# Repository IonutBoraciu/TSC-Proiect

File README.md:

# OpenBook, Boraciu Ionut-Sorin 335CA

# Description 

 OpenBook is an open-source, affordable e-book reader designed for mass production. The project focuses on accessibility, cost efficiency, and user control, providing a customizable reading experience with open hardware and software.

# Table of contents
1. [Description](#description)
2. [E-Book Reader Diagram](#e-book-reader-diagram)
3. [Bill of materials (BOM)](#bill-of-materials-bom)
4. [Hardware Functionality Description](#hardware-functionality-description)
5. [Estimated Power Consumption 🔋](#estimated-power-consumption-)
6. [Total estimated power consumtion ( assuming wifi active) 🔋](#total-estimated-power-consumtion--assuming-wifi-active-)
7. [Estimated battery life](#estimated-battery-life)
8. [ESP32-C6 Pin Usage](#esp32-c6-pin-usage)
9. [Pins explanation](#pins-explanation)
10. [Final Product](#final-product)

 # E-Book Reader Diagram

 # Bill of materials (BOM)
 | 🛠 Component | 🔗 Link | 📄 Datasheet |
 |-------------|--------|------------|
 | 112A-TAAR-R03_ATTEND |[Comet](https://store.comet.srl.ro/Catalogue/Product/43497/) | [Datasheet](https://store.comet.bg/download-file.php?id=27596) |
 | 744043680IND | [Mouser](https://eu.mouser.com/ProductDetail/Wurth-Elektronik/744043680?qs=PGXP4M47uW6VkZq%252BkzjrHA%3D%3D) | [Datasheet](https://www.we-online.com/components/products/datasheet/744043680.pdf) |
 | ADAFRUIT_LEDCHIP | [SnapMagic](https://www.snapeda.com/parts/KP-1608SURCK/Kingbright/view-part/?ref=search&t=LED%200603) | [Datasheet](https://www.snapeda.com/parts/KP-1608SURCK/Kingbright/datasheet/) |
 | BD5229G-TR | [Component Search Engine](https://componentsearchengine.com/part-view/BD5229G-TR/ROHM%20Semiconductor) | [Datasheet](https://datasheet.datasheetarchive.com/originals/distributors/Datasheets_SAMA/f2b9741ef86007909f138d561a359946.pdf) |
 | BUTTON_CUSYOMV1 | [Panasonic](https://industry.panasonic.com/global/en/products/control/switch/light-touch/number/evqpuj02k) | [Datasheet](https://industry.panasonic.com/global/en/downloads?tab=catalog&small_g_cd=203&part_no=EVQPUJ02K&q=RVZRUFVKMDJLJTdDMTMlN0MyMDMlN0MzNDU5JTdDMSU3QyU3QzIlN0NmYWxzZQ%3D%3D) |
 | CPH3225A | [SnapMagic](https://www.snapeda.com/parts/CPH3225A/Seiko+Instruments/view-part/?ref=eda) | [Datasheet](https://www.snapeda.com/parts/CPH3225A/Seiko%20Instruments/datasheet/) |
 | DS3231SN | [SnapMagic](https://www.snapeda.com/parts/DS3231SN%23/Analog+Devices/view-part/?ref=eda) | [Datasheet](https://www.snapeda.com/parts/DS3231SN%23/Analog%20Devices/datasheet/) |
 | EAGLE-LTSPICE_CC0402 | [Component Search Engine](https://componentsearchengine.com/part-view/CC0402MRX5R5BB106/YAGEO) | [Datasheet](https://componentsearchengine.com/Datasheets/2/CC0402MRX5R5BB106.pdf) |
 | ESP32-C6-WROOM-1-N8 | [SnapMagic](https://www.snapeda.com/parts/ESP32-C6-WROOM-1-N8/Espressif+Systems/view-part/?ref=eda) | [Datasheet](https://www.snapeda.com/parts/ESP32-C6-WROOM-1-N8/Espressif%20Systems/datasheet/) |
 | ESP32_WROVER_AVX | [Mouser](https://eu.mouser.com/ProductDetail/KYOCERA-AVX/SD0805S020S1R0?qs=jCA%252BPfw4LHbpkAoSnwrdjw%3D%3D) | [Datasheet](https://eu.mouser.com/datasheet/2/40/schottky-3165252.pdf) |
 | ESP32_WROVER_BME680_BME680 | [SnapMagic](https://www.snapeda.com/parts/BME680/Bosch/view-part/?welcome=home) | [Datasheet](https://www.snapeda.com/parts/BME680/Bosch%20Sensortec/datasheet/) |
 | ESP32_WROVER_EAGLE-LTSPICE_C | [Component Search Engine](https://componentsearchengine.com/part-view/CC0402MRX5R5BB106/YAGEO) | [Datasheet](https://componentsearchengine.com/Datasheets/2/CC0402MRX5R5BB106.pdf) |
 | ESP32_WROVER_EAGLE-LTSPICE_R | [Component Search Engine](https://componentsearchengine.com/part-view/R0402%201%25%20100%20K%20(RC0402FR-07100KL)/YAGEO) | [Datasheet](https://www.yageo.com/upload/media/product/products/datasheet/rchip/PYu-RC_Group_51_RoHS_L_12.pdf) |
 | ESP32_WROVER_SPARKFUN-DISCRETESEMI | [Component Search Engine](https://componentsearchengine.com/part-view/DMG2305UX-7/Diodes%20Incorporated) | [Datasheet](https://www.diodes.com//assets/Datasheets/DMG2305UX.pdf) |
 | ESP32_WROVER_SPARKFUN-IC-POWER_SOT23-5 | [Mouser](https://eu.mouser.com/ProductDetail/Microchip-Technology/MCP73831T-2ACI-OT?qs=yUQqVecv4qvbBQBGbHx0Mw%3D%3D) | [Datasheet](https://eu.mouser.com/datasheet/2/268/MCP73831_Family_Data_Sheet_DS20001984H-3441711.pdf) |
 | ESP32C6_VARISTORCN1812 | [Mouser](https://ro.mouser.com/ProductDetail/EPCOS-TDK/B72520T0350K062?qs=dEfas%2FXlABIszF52uu7vrg%3D%3D) | [Datasheet](https://www.tdk-electronics.tdk.com/inf/75/db/CTVS_14/Surge_protection_series.pdf) |
 | FH34SRJ24S05SH99 | [Component Search Engine](https://componentsearchengine.com/part-view/FH34SRJ-24S-0.5SH(99)/Hirose) | [Datasheet](https://www.hirose.com/en/product/document?clcode=CL0580-1255-6-99&productname=FH34SRJ-24S-0.5SH(99)&series=FH34SRJ&documenttype=2DDrawing&lang=en&documentid=0000990903) |
 | MAX17048G+T10 | [SnapMagic](https://www.snapeda.com/parts/MAX17048G+T10/Analog+Devices/view-part/?ref=eda) | [Datasheet](https://www.snapeda.com/parts/MAX17048G+T10/Analog%20Devices/datasheet/) |
 | MBR0530 | [Mouser](https://ro.mouser.com/ProductDetail/KYOCERA-AVX/SD0805S020S1R0?qs=jCA%252BPfw4LHbpkAoSnwrdjw%3D%3D) | [Datasheet](https://ro.mouser.com/datasheet/2/40/schottky-3165252.pdf) |
 | PGB1010603MR | [SnapMagic](https://www.snapeda.com/parts/PGB1010603MR/Littelfuse/view-part/?ref=eda) | [Datasheet](https://www.snapeda.com/parts/PGB1010603MR/Littelfuse%20Inc./datasheet/) |
 | QWIIC_CONNECTORJS | [Mouse](https://eu.mouser.com/ProductDetail/Adafruit/4208?qs=PzGy0jfpSMtbScLbr0L5dw%3D%3D) | [Datasheet](https://www.youtube.com/watch?v=Z6ACqvqwDWE) |
 | SAMACSYS_PARTS_USB4110-GF-A | [Component Search Engine](https://componentsearchengine.com/part-view/USB4110-GF-A/GCT%20(GLOBAL%20CONNECTOR%20TECHNOLOGY)) | [Datasheet](https://gct.co/files/drawings/usb4110.pdf) |
 | SI1308EDL-T1-GE3 | [Component Search Engine](https://componentsearchengine.com/part-view/SI1308EDL-T1-GE3/Vishay) | [Datasheet](https://componentsearchengine.com/Datasheets/1/SI1308EDL-T1-GE3.pdf) |
 | SJ | [GrabCAD](https://grabcad.com/library/solder-jumpers-1) | [Datasheet](https://www.youtube.com/watch?v=Z6ACqvqwDWE) |
 | USBLC6-2SC6Y | [SnapMagic](https://www.snapeda.com/parts/USBLC6-2SC6Y/STMicroelectronics/view-part/?ref=eda) | [Datasheet](https://www.snapeda.com/parts/USBLC6-2SC6Y/STMicroelectronics/datasheet/) |
 | W25Q512JVEIQ | [SnapMagic](https://www.snapeda.com/parts/W25Q512JVEIQ/Winbond+Electronics/view-part/?ref=eda) | [Datasheet](https://www.snapeda.com/parts/W25Q512JVEIQ/Winbond%20Electronics/datasheet/) |
 | XC6220A331MR-G | [Component Search Engine](https://componentsearchengine.com/part-view/XC6220A331MR-G/Torex) | [Datasheet](https://product.torexsemi.com/system/files/series/xc6220.pdf) |

# Hardware Functionality Description

### 1. Battery 🔋
 Model: CELLEVIA BATTERIES LP584174 <br>
 Specifications: 3.7V, 1800mAh  <br>
 Functionality: It is rechargeable battery, designed for portable electronic devices. It provides a stable power supply, high energy density, and a lightweight form factor. Ideal for IoT devices, wearables, embedded systems, and battery powered applications, it ensures reliable performance with a long cycle life.

 ### 2. ESP32-C6 📡
 Model: ESP32-C6-WROOM-1 <br>
 Specifications:
  * 2.4 GHz Wi-Fi 6 (802.11 ax)
  *  Bluetooth® 5 (LE) with Long Range support
  *  Zigbee and Thread(802.15.4) for low-power mesh networking  <br>
  
  Functionality: The ESP32-C6-WROOM-1 is the central controller of the project, handling all communication, control, and processing

  ### 3. E-Paper Display 📺
  Model: 7.5inch e-Paper V2 <br>
  Specifications: resolution : 800 x 480, weight ~ 44 g <br>
  Functionality: The 7.5-inch e-Paper V2 display provides a high contrast, low power visual output suitable for battery-powered applications. Unlike traditional displays, it retains content without power, making it ideal for low energy and always on applications.

 ### 4. BME688 🌡️
 Interface: I2C <br>
 Specifications:
  * Gas Sensor: Detects volatile organic compounds, carbon monoxide, hydrogen, and other gases
  * Humidity Sensor: 0–100% RH, accuracy ±3%
  * Temperature Sensor: -40°C to 85°C, accuracy ±0.5°C
  * Pressure Sensor: 300–1100 hPa, accuracy ±0.6 hPa <br>
  
 Functionality: The BME688 is an advanced environmental sensing module, providing real-time monitoring of air quality, humidity, temperature, and pressure.

 ### 5. SD Card 💾
 Interface: SPI <br>
 Functionality: it serves as expandable storage, allowing users to store a large collection of e-books, documents, and other files beyond the device's internal memory

 ### 6. RTC ⏰
 Interface: I2C <br>
 Functionality: A real-time clock (RTC) keeps track of the correct time and date, even when the device is off. It helps manage power saving features, timestamps activities like reading progress, supports reminder functions, updates time-sensitive content, and ensures proper synchronization with other devices or platforms.

 ### 7. MCP73831T ♻️🔋
 Interface: USB-C <br>
 Functionality: The MCP73831T is a compact lithium-ion and lithium-polymer battery charger IC. It features low power consumption, precharge and fast charge modes, thermal regulation, and overvoltage protection, making it ideal for portable devices.

 ### 8. External NOR Flash 64MB 🎞️
 Interface: SPI <br>
 Functionality:  non-volatile memory storage that provides 64MB of data storage. It's commonly used in embedded systems and devices for storing firmware, code, or other critical data, offering fast read speeds and reliable data retention even without power.

 ### 9. LDO Voltage Regulator ⚡
 Functionality: voltage regulator that provides a stable output voltage with minimal difference between the input and output voltages.

 ### 10. Test Pads 📝
 Functionality: deubbing and testing outputs from certain components.

 ### 11. Qwiic ✅
 Functionality: easy addition of modules through I2C and SPI.

 # Estimated Power Consumption 🔋

 ### 1. Battery (CELLEVIA BATTERIES LP584174) 🔋
  * Its power consumption depends on the load it is powering. The maximum discharge current would be around 1.8A (1800mAh)
### 2. ESP32-C6 📡
  * Wi-Fi transmission: ~200mA
  * Idle mode: ~50mA
  * Deep sleep: ~10mA
### 3. E-Paper Display 📺
  * During content update: ~30-50mA
  * Idle (static content): ~0mA (only power used for maintaining the display)
### 4. BME688 🌡️
 * Active sensing: ~2.7mA
 * Idle mode: ~0.5mA (depends on the sleep settings)
### 5. SD Card 💾
 * Typical: ~10-15 mA
### 6. RTC ⏰
* Active mode: 1- 2 mA
### 7. MCP73831T ♻️🔋
*  Minimal power consumption
### 8. External NOR Flash 64MB 🎞️
* Active read/write: ~10-20mA
* Idle: <1mA
### 9. LDO Voltage Regulator ⚡
 * Idle mode: ~1-10mA (depends on the output load)
### 10. Test Pads 📝
* Minimal power consumption, essentially 0mA unless active signals are being tested.
### 11. Qwiic ✅
* Active communication: ~5-10mA (depends on the connected module)

# Total estimated power consumtion ( assuming wifi active) 🔋

 | 🛠 Component | Power estimation 🔋
 |-------------|--------|
 | ESP32-C6 | 200 mA |
 | E-Paper Display | 50 mA |
 | BME688 | 2.7 mA |
 | SD Card | 15 mA |
 | RTC | 2 mA |
 | External NOR Flash | 20 mA |
 | LDO Voltage Regulator | 10 mA |
 | Qwiic | 10 mA |

Total = 200mA + 50mA + 2.7mA + 15mA + 2mA + 20mA + 10mA + 10mA = 309.7mA

# Estimated battery life

**Battery life = 1800 mAh / 309.7 mA = 5.81 hours**

# ESP32-C6 Pin Usage

## Power connections 🔋
* Pin 2 ( 3V3) - provides 3.3V to the ESP32-C6
* Ground ( bottom-right pin) - provides ground connection

## Reset and Boot 🔁
* Pin 3 ( Reset) - manual reset pin
* Pin 15 ( IO/BOOT) - boot mode selection, pulled down by a 10K resistor

## I2C 📡
* Pin 8 ( INT_RTC) - interrupt signal from RTC
* Pin 16 ( RTC_RST) - reset for RTC
* Pin 18 ( I2C_PW) - power enable signal for I2C devices
* Pin 20 ( SDA) - data line for I2C comms
* Pin 21 ( SCL) - clock line for I2C comms

## SPI 🛰️
* Pin 4 ( SS_SD) - slave select for SD card
* Pin 7 ( SCK) - Serial clock used for synchronizing SPI comms
* Pin 10 ( MOSI) - Master Out Slave In, sending data to components
* Pin 11 ( EPD_CS) - chip select for e-paper display
* Pin 12 ( FLASH_CS) - chip select for flash memory
* Pin 27 ( MISO)  - Master In Slave Out, used for reading data from components

## E-Paper Display Control Signals 🖥️
* Pin 5 ( EPD_DC) - data control for E-Paper Display
* Pin 19 ( EPD_3V3_C) - enable pin for EPD power
* Pin 21 ( EPD_RST) - reset pin for E-Paper Display
* Pin 26 ( EPD_BUSY) - indicates when E-Paper Display is busy

## USB 🔌
* Pin 13 ( USB_D-) + Pin 14 ( USB_D+) - differential data lines for USB comms

## UART 🔧
* Pin 24 ( RX) - UART receive pin
* Pin 25 ( TX) - UART transmit pin

## Others ⚙️
* Pin 23 ( IO_CHANGE)  - interrupt or status for external components

# Pins explanation

* SPI (Serial Peripheral Interface) is used for high speed comms with the Flash and E-Paper Display.
* I2C low speed comms with sensor ( RTC).
* UART pins ( TX, RX) debugging and external serial comms.
* Dedicated control pins ( EPD_BUSY, EPD_DC) ensure efficient E-Paper operation.

# Final Product

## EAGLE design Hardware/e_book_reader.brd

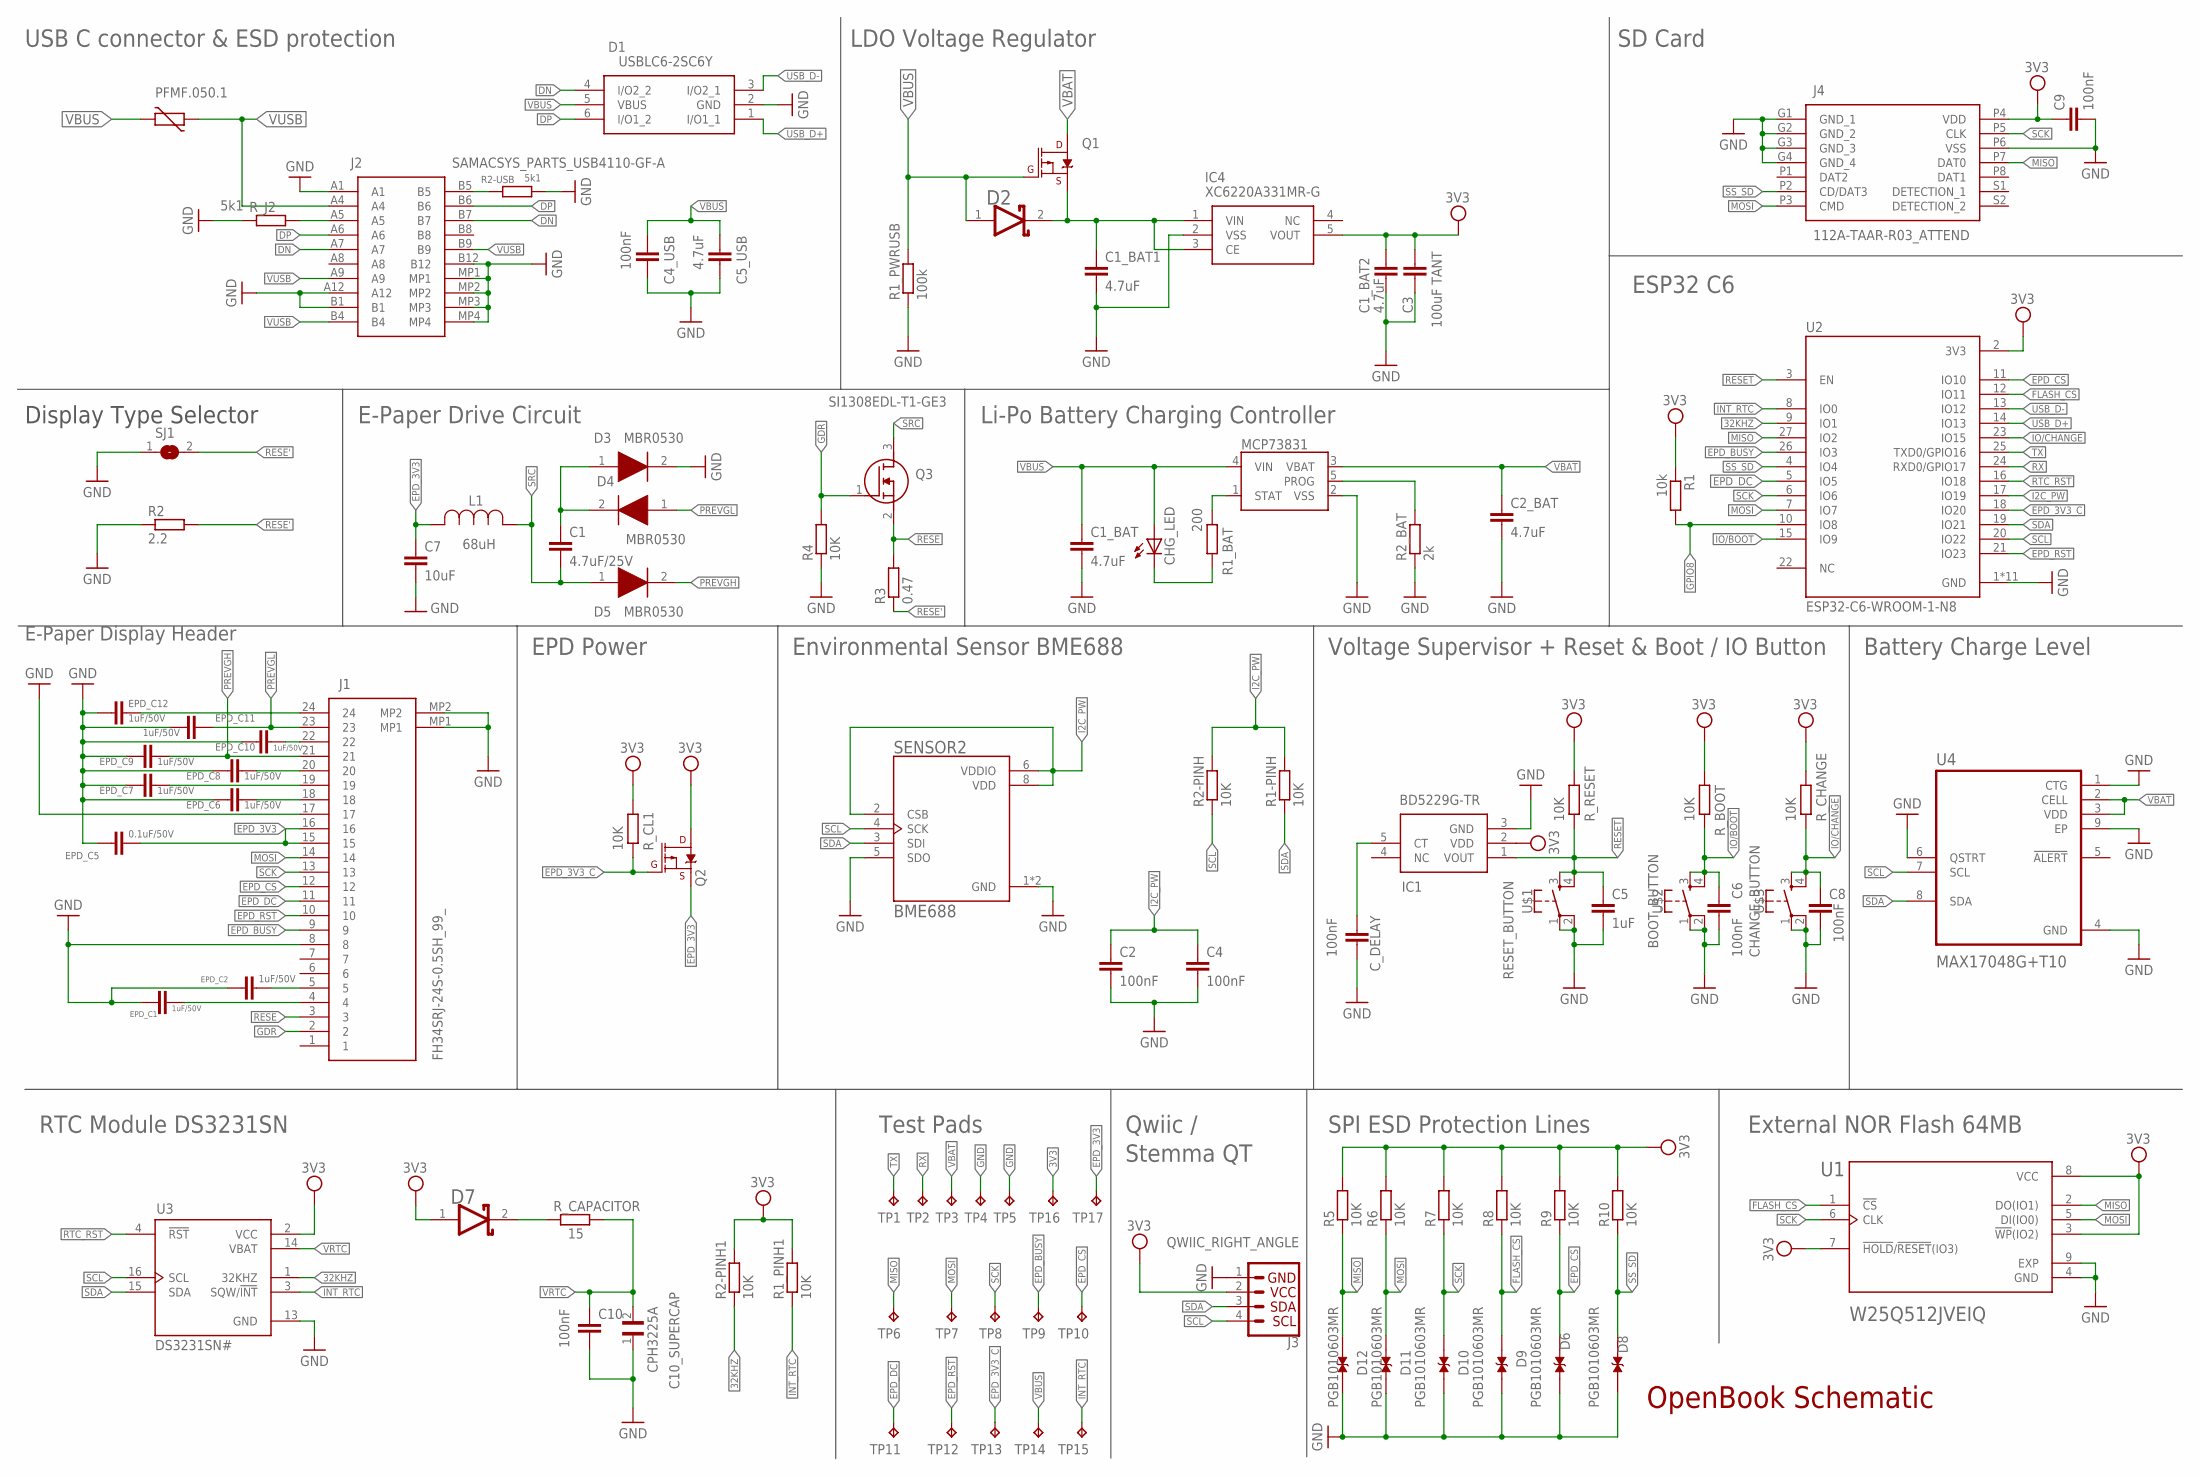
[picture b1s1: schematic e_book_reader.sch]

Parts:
C1: 4.7uF/25V; ESP32_WROVER_EAGLE-LTSPICE_C0402
C1_BAT, C1_BAT1, C1_BAT2, C2_BAT, C5_USB: 4.7uF; ESP32_WROVER_EAGLE-LTSPICE_C0402
C2, C4, C4_USB, C8, C9, C10: 100nF; ESP32_WROVER_EAGLE-LTSPICE_C0402
C3: 100uF TANT; ESP32_WROVER_EAGLE-LTSPICE_C0402
C5: 1uF; EAGLE-LTSPICE_C0402
C6: 100nF; EAGLE-LTSPICE_C0402
C7: 10uF; ESP32_WROVER_EAGLE-LTSPICE_C0402
C10_SUPERCAP: CPH3225A; CAPCP3225X100N
CHG_LED: ADAFRUIT_LEDCHIP-LED0603; ADAFRUIT_CHIP-LED0603
C_DELAY: 100nF; ESP32_WROVER_EAGLE-LTSPICE_C0402
D1: USBLC6-2SC6Y; SOT95P280X145-6N
D2, D7: ESP32_WROVER_AVX---SD0805S020S1R0_AVX_SD0805S020S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; ESP32_WROVER_AVX---SD0805S020S1R0_AVX_SD0805S020S1R0_0
D3, D4, D5: MBR0530; SOD3716X135N
D6, D8, D9, D10, D11, D12: PGB1010603MR; DIOC1608X36N
EPD_C1, EPD_C2, EPD_C6, EPD_C7, EPD_C8, EPD_C9, EPD_C10, EPD_C11, EPD_C12: 1uF/50V; ESP32_WROVER_EAGLE-LTSPICE_C0402
EPD_C5: 0.1uF/50V; ESP32_WROVER_EAGLE-LTSPICE_C0402
IC1: BD5229G-TR; SOT95P280X125-5N
IC4: XC6220A331MR-G; SOT95P280X120-5N
J1: FH34SRJ-24S-0.5SH_99_; FH34SRJ24S05SH99
J2: SAMACSYS_PARTS_USB4110-GF-A; SAMACSYS_PARTS_USB4110GFA
J3: QWIIC_RIGHT_ANGLE; JST04_1MM_RA
J4: 112A-TAAR-R03_ATTEND; 112ATAARR03ATTEND
L1: 68uH; IND_4828-WE-TPC_WRE
MCP73831: ESP32_WROVER_SPARKFUN-IC-POWER_MCP73831; ESP32_WROVER_SPARKFUN-IC-POWER_SOT23-5
PFMF.050.1: ESP32C6_VARISTORCN1812; ESP32C6_VARISTOR_CT/CN1812
Q1, Q2: ESP32_WROVER_SPARKFUN-DISCRETESEMI_MOSFET_PCH; ESP32_WROVER_SPARKFUN-DISCRETESEMI_SOT23-3
Q3: SI1308EDL-T1-GE3; SOT65P210X110-3N
R1: 10k; ESP32_WROVER_EAGLE-LTSPICE_R0402
R1-PINH, R1_PINH1, R2-PINH, R2-PINH1, R4, R5, R6, R7, R8, R9, R10: 10K; ESP32_WROVER_EAGLE-LTSPICE_R0402
R1_BAT: 200; ESP32_WROVER_EAGLE-LTSPICE_R0402
R1_PWRUSB: 100k; ESP32_WROVER_EAGLE-LTSPICE_R0402
R2: 2.2; ESP32_WROVER_EAGLE-LTSPICE_R0402
R2-USB: 5k1; ESP32_WROVER_EAGLE-LTSPICE_R0402
R2_BAT: 2k; ESP32_WROVER_EAGLE-LTSPICE_R0402
R3: 0.47; ESP32_WROVER_EAGLE-LTSPICE_R0402
R_BOOT: 10K; ESP32_WROVER_EAGLE-LTSPICE_R0402
R_CAPACITOR: 15; ESP32_WROVER_EAGLE-LTSPICE_R0402
R_CHANGE: 10K; ESP32_WROVER_EAGLE-LTSPICE_R0402
R_CL1: 10K; ESP32_WROVER_EAGLE-LTSPICE_R0402
R_J2: 5k1; ESP32_WROVER_EAGLE-LTSPICE_R0402
R_RESET: 10K; ESP32_WROVER_EAGLE-LTSPICE_R0402
SENSOR2: BME688; ESP32_WROVER_BME680_PSON80P300X300X100-8N
SJ1: SJ
TP1, TP2, TP3, TP4, TP5, TP6, TP7, TP8, TP9, TP10, TP11, TP12, TP13, TP14, TP15, TP16: TPTP20R; TP20R
TP17: TP; TP20R
U1: W25Q512JVEIQ; SON127P600X800X80-9N
U2: ESP32-C6-WROOM-1-N8; XCVR_ESP32-C6-WROOM-1-N8
U3: DS3231SN#; SOIC127P1032X265-16N
U4: MAX17048G+T10; SON50P200X200X80-9N
U$1: RESET_BUTTON; MYBUTTON
U$2: BOOT_BUTTON; MYBUTTON
U$3: CHANGE_BUTTON; MYBUTTON

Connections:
3V3: C1_BAT2.1, C3.1, C9.1, D7.1 (ANODE), IC1.2 (VDD), IC4.5 (VOUT), J3.2, J4.P4 (VDD), Q2.1 (D), R1.1, R1_PINH1.2, R2-PINH1.2, R5.2, R6.2, R7.2, R8.2, R9.2, R10.2, R_BOOT.2, R_CHANGE.2, R_CL1.2, R_RESET.2, TP16.TP, U1.3 (!WP!(IO2)), U1.7 (!HOLD!/!RESET!(IO3)), U1.8 (VCC), U2.2 (3V3), U3.2 (VCC)
32KHZ: R2-PINH1.1, U2.9 (IO1), U3.1 (32KHZ)
DN: D1.4 (I/O2_2), J2.A7, J2.B7
DP: D1.6 (I/O1_2), J2.A6, J2.B6
EPD_3V3: C7.1, EPD_C5.1, J1.15, J1.16, L1.2, Q2.3 (S), TP17.TP
EPD_3V3_C: Q2.2 (G), R_CL1.1, TP13.TP, U2.18 (IO20)
EPD_BUSY: J1.9, TP9.TP, U2.26 (IO3)
EPD_CS: D6.1, J1.12, R9.1, TP10.TP, U2.11 (IO10)
EPD_DC: J1.11, TP11.TP, U2.5 (IO5)
EPD_RST: J1.10, TP12.TP, U2.21 (IO23)
FLASH_CS: D9.1, R8.1, U1.1 (!CS), U2.12 (IO11)
GDR: J1.2, Q3.1 (G), R4.2
GND: C1_BAT.2, C1_BAT1.2, C1_BAT2.2, C2.2, C2_BAT.2, C3.2, C4.2, C4_USB.2, C5.2, C5_USB.2, C6.2, C7.2, C8.2, C9.2, C10.2, C10_SUPERCAP.1, C_DELAY.2, D1.2 (GND), D3.2 (K), D6.2, D8.2, D9.2, D10.2, D11.2, D12.2, EPD_C1.2, EPD_C2.2, EPD_C5.2, EPD_C6.2, EPD_C7.2, EPD_C8.2, EPD_C9.2, EPD_C10.2, EPD_C11.2, EPD_C12.2, IC1.3 (GND), IC4.2 (VSS), J1.8, J1.17, J1.MP1, J1.MP2, J2.A1, J2.A12, J2.B1, J2.B12, J2.MP1, J2.MP2, J2.MP3, J2.MP4, J3.1, J4.G1 (GND_1), J4.G2 (GND_2), J4.G3 (GND_3), J4.G4 (GND_4), J4.P6 (VSS), MCP73831.2 (VSS), R1_PWRUSB.1, R2.1, R2-USB.2, R2_BAT.1, R4.1, R_J2.1, SENSOR2.1 (GND), SENSOR2.5 (SDO), SENSOR2.7 (GND), SJ1.1, TP4.TP, TP5.TP, U1.4 (GND), U1.9 (EXP), U2.1 (GND), U2.28 (GND), U2.29_1 (GND), U2.29_2 (GND), U2.29_3 (GND), U2.29_4 (GND), U2.29_5 (GND), U2.29_6 (GND), U2.29_7 (GND), U2.29_8 (GND), U2.29_9 (GND), U3.13 (GND), U4.1 (CTG), U4.4 (GND), U4.6 (QSTRT), U4.9 (EP), U$1.1, U$1.2, U$2.1, U$2.2, U$3.1, U$3.2
GPIO8: R1.2, U2.10 (IO8)
I2C_PW: C2.1, C4.1, R1-PINH.2, R2-PINH.2, SENSOR2.2 (CSB), SENSOR2.6 (VDDIO), SENSOR2.8 (VDD), U2.17 (IO19)
INT_RTC: R1_PINH1.1, TP15.TP, U2.8 (IO0), U3.3 (SQW/!INT)
IO/BOOT: C6.1, R_BOOT.1, U2.15 (IO9), U$2.3, U$2.4
IO/CHANGE: C8.1, R_CHANGE.1, U2.23 (IO15), U$3.3, U$3.4
MISO: D12.1, J4.P7 (DAT0), R5.1, TP6.TP, U1.2 (DO(IO1)), U2.27 (IO2)
MOSI: D11.1, J1.14, J4.P3 (CMD), R6.1, TP7.TP, U1.5 (DI(IO0)), U2.7 (IO7)
unnamed: J2.A5, R_J2.2
unnamed: MCP73831.1 (STAT), R1_BAT.2
unnamed: J2.B5, R2-USB.1
unnamed: C1_BAT1.1, D2.2 (CATHODE), IC4.1 (VIN), IC4.3 (CE), Q1.3 (S)
unnamed: C1.1, D3.1 (A), D4.2 (K)
unnamed: CHG_LED.C, R1_BAT.1
unnamed: MCP73831.5 (PROG), R2_BAT.2
unnamed: EPD_C1.1, J1.4
unnamed: EPD_C6.1, J1.18
unnamed: EPD_C2.1, J1.5
unnamed: EPD_C7.1, J1.19
unnamed: EPD_C8.1, J1.20
unnamed: EPD_C10.1, J1.22
unnamed: EPD_C12.1, J1.24
unnamed: C_DELAY.1, IC1.5 (CT)
unnamed: D7.2 (CATHODE), R_CAPACITOR.1
PREVGH: D5.2 (K), EPD_C9.1, J1.21
PREVGL: D4.1 (A), EPD_C11.1, J1.23
RESE: J1.3, Q3.2 (S), R3.2
RESE': R2.2, R3.1, SJ1.2
RESET: C5.1, IC1.1 (VOUT), R_RESET.1, U2.3 (EN), U$1.3, U$1.4
RTC_RST: U2.16 (IO18), U3.4 (!RST)
RX: TP2.TP, U2.24 (RXD0/GPIO17)
SCK: D10.1, J1.13, J4.P5 (CLK), R7.1, TP8.TP, U1.6 (CLK), U2.6 (IO6)
SCL: J3.4, R2-PINH.1, SENSOR2.4 (SCK), U2.20 (IO22), U3.16 (SCL), U4.7 (SCL)
SDA: J3.3, R1-PINH.1, SENSOR2.3 (SDI), U2.19 (IO21), U3.15 (SDA), U4.8 (SDA)
SRC: C1.2, D5.1 (A), L1.1, Q3.3 (D)
SS_SD: D8.1, J4.P2 (CD/DAT3), R10.1, U2.4 (IO4)
TX: TP1.TP, U2.25 (TXD0/GPIO16)
USB_D+: D1.1 (I/O1_1), U2.14 (IO13)
USB_D-: D1.3 (I/O2_1), U2.13 (IO12)
VBAT: C2_BAT.1, MCP73831.3 (VBAT), Q1.1 (D), TP3.TP, U4.2 (CELL), U4.3 (VDD)
VBUS: C1_BAT.1, C4_USB.1, C5_USB.1, CHG_LED.A, D1.5 (VBUS), D2.1 (ANODE), MCP73831.4 (VIN), PFMF.050.1.2, Q1.2 (G), R1_PWRUSB.2, TP14.TP
VRTC: C10.1, C10_SUPERCAP.2, R_CAPACITOR.2, U3.14 (VBAT)
VUSB: J2.A4, J2.A9, J2.B4, J2.B9, PFMF.050.1.1

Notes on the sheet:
USB C connector & ESD protection
LDO Voltage Regulator
SD Card
Display Type Selector
E-Paper Drive Circuit
Li-Po Battery Charging Controller
ESP32 C6
E-Paper Display Header
EPD Power
Environmental Sensor BME688
Voltage Supervisor + Reset & Boot / IO Button
Battery Charge Level
RTC Module DS3231SN
Test Pads
Qwiic /
Stemma QT
SPI ESD Protection Lines
OpenBook Schematic
External NOR Flash 64MB

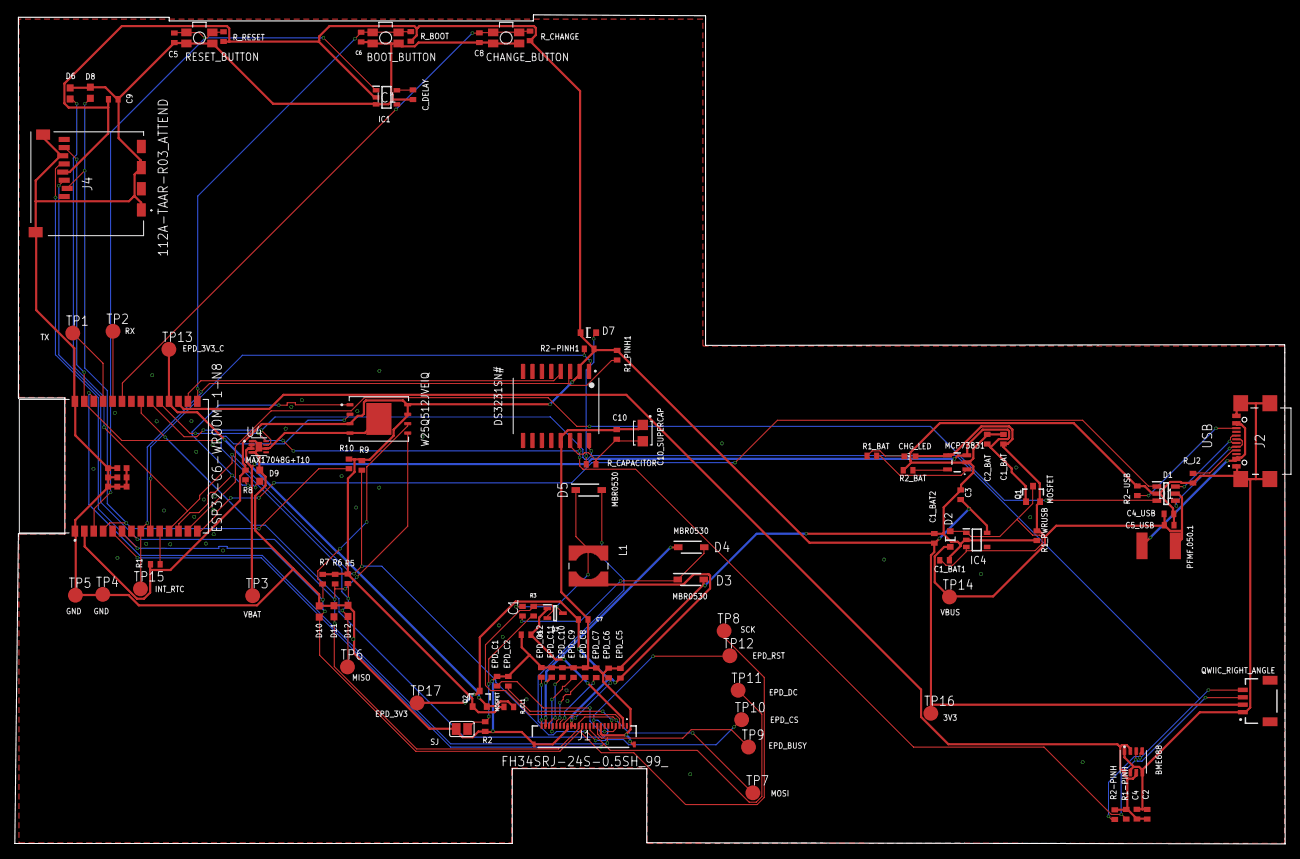
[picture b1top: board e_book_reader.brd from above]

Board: 2 copper layers, 171.3 x 111.8 mm, 103 parts (0 on the bottom side), 55 nets.

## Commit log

2025-04-04 added board and schematic
2025-04-04 Finished BOM
2025-04-04 Added hardware functionality description
2025-04-04 added estimated power consumtion
2025-04-05 added CPL file
2025-04-05 added bill of materials
2025-04-05 added gerbers arhive
2025-04-05 added 3D model
2025-04-05 added exploaded view
2025-04-05 added a few images
2025-04-05 changed name
2025-04-05 added GNU license
2025-04-05 fixed issue
2025-04-05 fixing
2025-04-05 Create LICENSE
2025-04-12 fixed issues
2025-04-12 updated photo of 3D board
2025-04-12 updated 3D image

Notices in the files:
parts and their libraries:
COPYRIGHT: Copyright (C) 2024 Ultra Librarian. All rights reserved.
